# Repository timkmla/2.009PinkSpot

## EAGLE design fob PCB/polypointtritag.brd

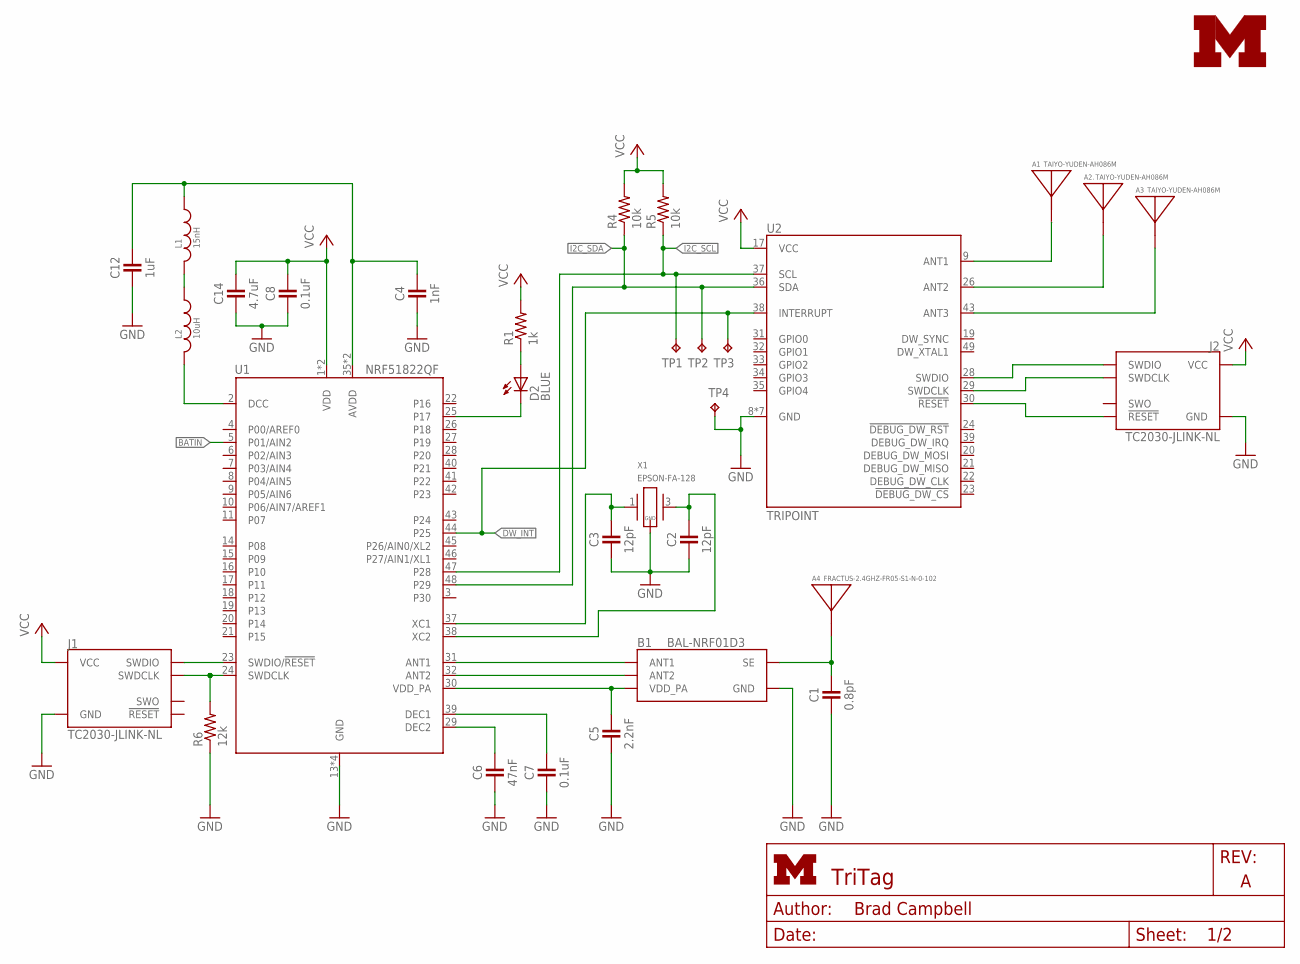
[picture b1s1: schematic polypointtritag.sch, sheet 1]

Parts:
A1, A2., A3: TAIYO-YUDEN-AH086M
A4: FRACTUS-2.4GHZ-FR05-S1-N-0-102; FRACTUS-ANTENNA-FR05-S1-N-0-102
B1: BAL-NRF01D3
C1: 0.8pF; 0402_CAP
C2, C3: 12pF; 0402_CAP
C4: 1nF; 0402_CAP
C5: 2.2nF; 0402_CAP
C6: 47nF; 0402_CAP
C7, C8: 0.1uF; 0402_CAP
C12: 1uF; 0402_CAP
C14: 4.7uF; 0402_CAP
D2: BLUE; LED-0603
J1, J2: TC2030-JLINK-NL; TC2030-IDC-NL
L1: 15nH; 0402_CAP
L2: 10uH; 0603_CAP
LOGO1: UMICH_SOLID_SMALL; UMICH_SOLID_75MIL
R1: 1k; 0402_RES
R4, R5: 10k; 0402_RES
R6: 12k; 0402_RES
TP1, TP2, TP3, TP4: TPTP06SQ; TP06SQ
U1: NRF51822QF; QFN-48-6MM
U2: TRIPOINT
X1: EPSON-FA-128; FA-128

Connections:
!CHRG1: D2.A, R1.1
ANTENNA: A4.1, B1.SE, C1.1
AVDD: C4.1, C12.1, L1.1, U1.35 (AVDD), U1.36 (AVDD)
BATIN: U1.5 (P01/AIN2); also elsewhere on the board
DCC: L2.2, U1.2 (DCC)
DW_INT: TP3.TP, U1.44 (P25), U2.38 (INTERRUPT)
GND: B1.GND, C1.2, C2.2, C3.2, C4.2, C5.2, C6.2, C7.2, C8.2, C12.2, C14.2, J1.5 (GND), J2.5 (GND), R6.1, TP4.TP, U1.13 (GND), U1.33 (GND), U1.34 (GND), U1.GND, U2.8 (GND), U2.10 (GND), U2.18 (GND), U2.25 (GND), U2.27 (GND), U2.42 (GND), U2.44 (GND), X1.2 (GND), X1.4 (GND); also elsewhere on the board
I2C_SCL: R5.1, TP1.TP, U1.47 (P28), U2.37 (SCL)
I2C_SDA: R4.1, TP2.TP, U1.48 (P29), U2.36 (SDA)
unnamed: A1.A, U2.9 (ANT1)
unnamed: A2..A, U2.26 (ANT2)
unnamed: A3.A, U2.43 (ANT3)
unnamed: J2.2 (SWDIO), U2.28 (SWDIO)
unnamed: D2.C, U1.25 (P17)
unnamed: J2.4 (SWDCLK), U2.29 (SWDCLK)
unnamed: J2.3 (!RESET), U2.30 (!RESET)
unnamed: C3.1, U1.37 (XC1), X1.1
unnamed: C2.1, U1.38 (XC2), X1.3 (2)
unnamed: C6.1, U1.29 (DEC2)
unnamed: C7.1, U1.39 (DEC1)
unnamed: B1.ANT1, U1.31 (ANT1)
unnamed: B1.ANT2, U1.32 (ANT2)
unnamed: B1.VCC (VDD_PA), C5.1, U1.30 (VDD_PA)
unnamed: L1.2, L2.1
SWDCLK: J1.4 (SWDCLK), R6.2, U1.24 (SWDCLK)
SWDIO/!RESET: J1.2 (SWDIO), U1.23 (SWDIO/!RESET)
VCC: C8.1, C14.1, J1.1 (VCC), J2.1 (VCC), R1.2, R4.2, R5.2, U1.1 (VDD), U1.12 (VDD), U2.17 (VCC); also elsewhere on the board

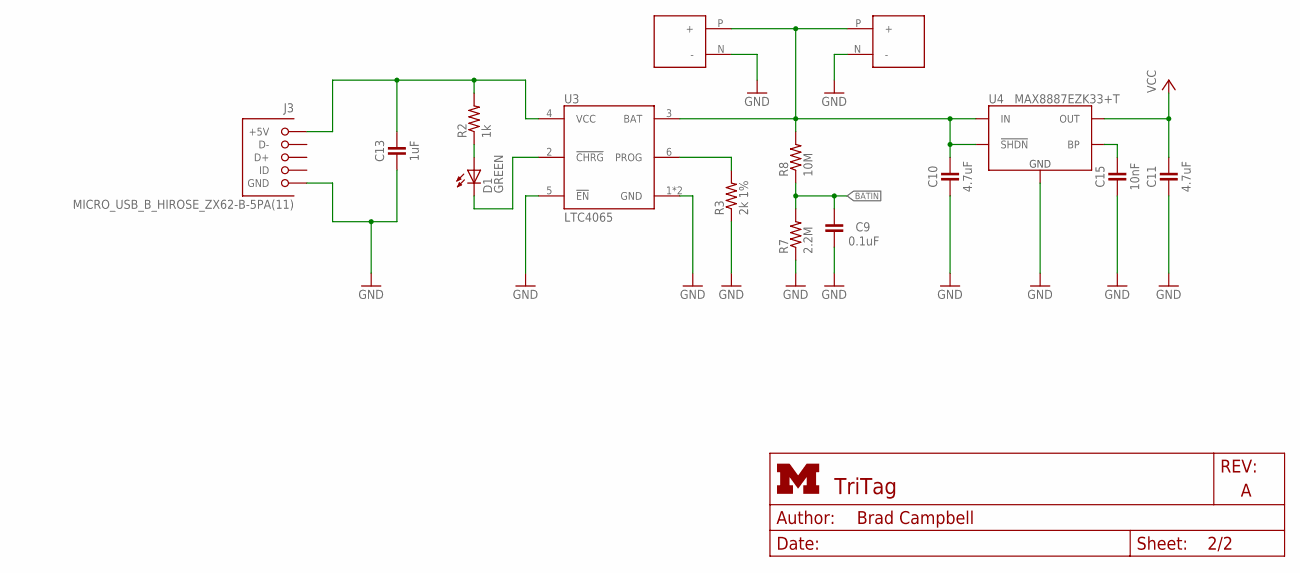
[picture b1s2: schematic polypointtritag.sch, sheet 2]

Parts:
C9: 0.1uF; 0402_CAP
C10, C11: 4.7uF; 0402_CAP
C13: 1uF; 0402_CAP
C15: 10nF; 0402_CAP
D1: GREEN; LED-0603
J3: MICRO_USB_B_HIROSE_ZX62-B-5PA(11); USB_MICRO_B-HIROSE-ZX62-B-5PA(11)
J4, J5: BAT_HOLE; BATTERY_HOLE
R2: 1k; 0402_RES
R3: 2k 1%; 0402_RES
R7: 2.2M; 0402_RES
R8: 10M; 0402_RES
U3: LTC4065; DFN-6/2MM
U4: MAX8887EZK33+T; SOT-23-5

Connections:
!CHRG: D1.A, R2.1
BATIN: C9.2, R7.2, R8.1; also elsewhere on the board
GND: C9.1, C10.2, C11.2, C13.2, C15.2, J3.5 (GND), J4.N (-), J5.N (-), R3.1, R7.1, U3.1 (GND), U3.5 (!EN), U3.7 (GND), U4.2 (GND); also elsewhere on the board
unnamed: D1.C, U3.2 (!CHRG)
unnamed: C15.1, U4.4 (BP)
unnamed: R3.2, U3.6 (PROG)
VBAT: C10.1, J4.P (+), J5.P (+), R8.2, U3.3 (BAT), U4.1 (IN), U4.3 (!SHDN)
VCC: C11.1, U4.5 (OUT); also elsewhere on the board
VUSB: C13.1, J3.1 (+5V), R2.2, U3.4 (VCC)

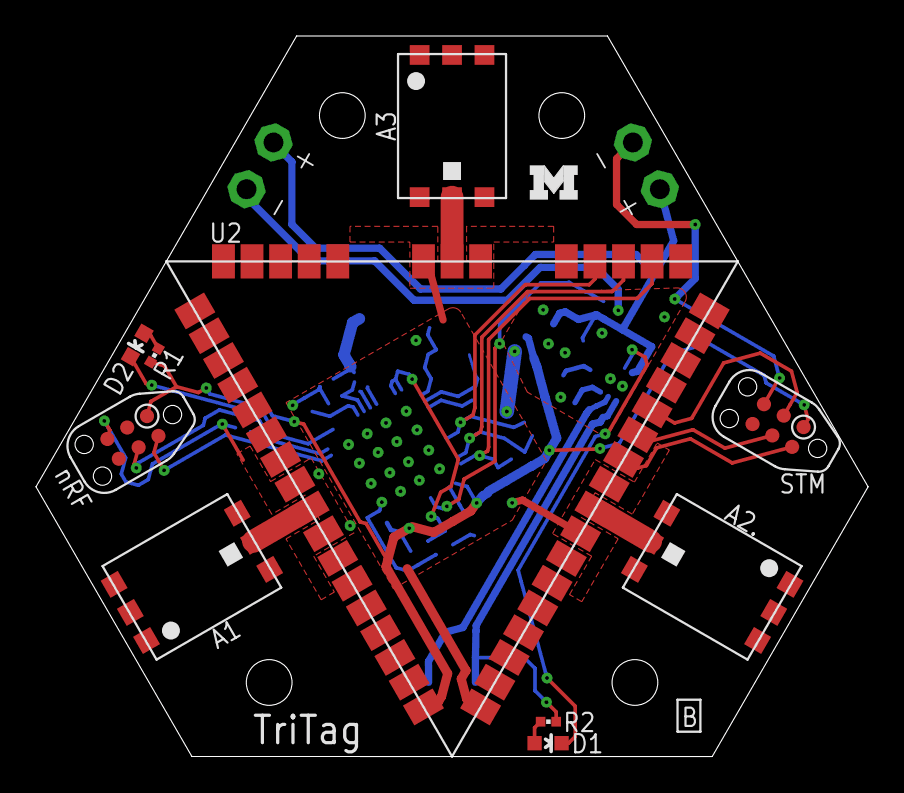
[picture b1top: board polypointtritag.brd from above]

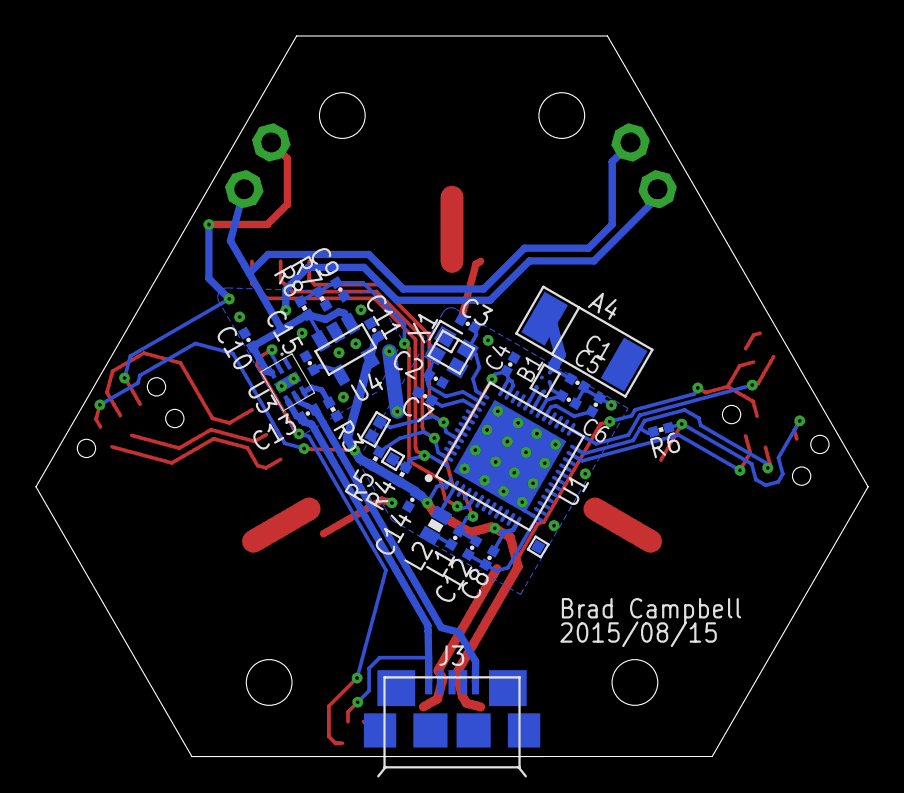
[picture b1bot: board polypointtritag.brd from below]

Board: 2 copper layers, 46.2 x 40.0 mm, 47 parts (34 on the bottom side), 33 nets.

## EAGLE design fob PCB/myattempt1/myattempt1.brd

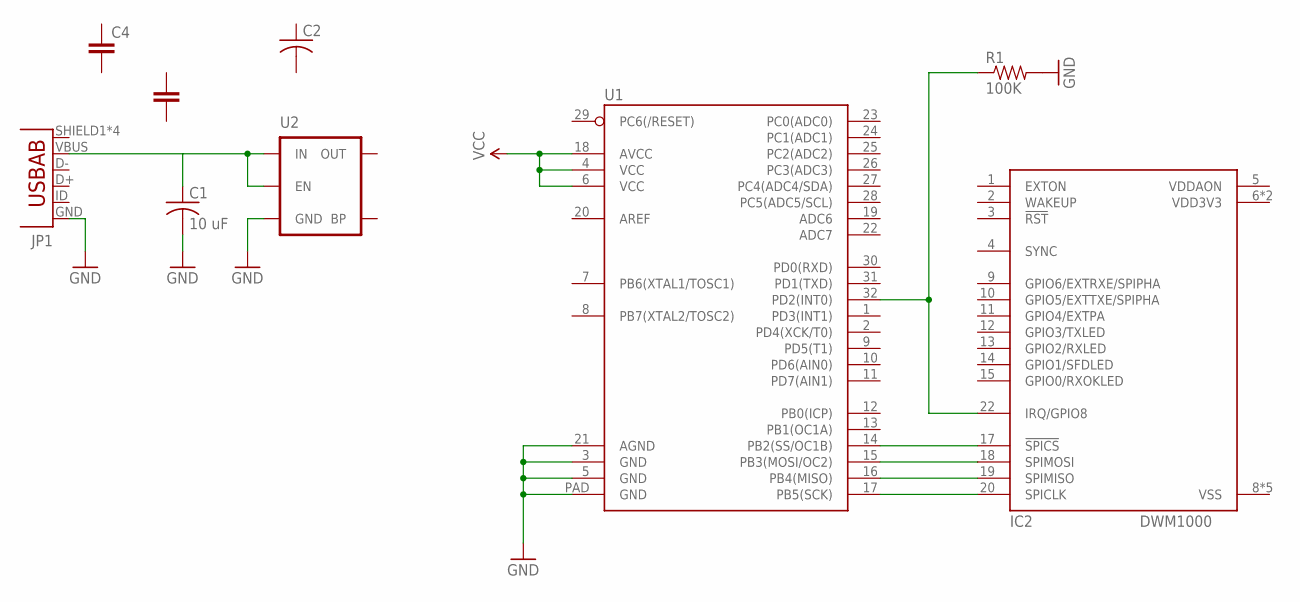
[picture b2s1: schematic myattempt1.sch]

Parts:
C1: 10 uF; C025-024X044
C2: C-US025-024X044; C025-024X044
C4: CAP0402-CAP; 0402-CAP
IC2: DWM1000
JP1: USB-AB; USB-AB-MICRO-SMD
R1: 100K; 0402-RES
U1: ATMEGA328P_MLFMLF32; MLF32-PAD
U2: MIC52053.3V; SOT23-5

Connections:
GND: C1.2, JP1.GND, R1.2, U1.3 (GND), U1.5 (GND), U1.21 (AGND), U1.PAD (GND), U2.2 (GND)
unnamed: IC2.20 (SPICLK), U1.17 (PB5(SCK))
unnamed: IC2.19 (SPIMISO), U1.16 (PB4(MISO))
unnamed: IC2.18 (SPIMOSI), U1.15 (PB3(MOSI/OC2))
unnamed: IC2.22 (IRQ/GPIO8), R1.1, U1.32 (PD2(INT0))
unnamed: IC2.17 (!SPICS), U1.14 (PB2(SS/OC1B))
unnamed: C1.1, JP1.VBUS, U2.1 (IN), U2.3 (EN)
VCC: U1.4 (VCC), U1.6 (VCC), U1.18 (AVCC)

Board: 2 copper layers, 8 parts (0 on the bottom side), 8 nets, no tracks yet.

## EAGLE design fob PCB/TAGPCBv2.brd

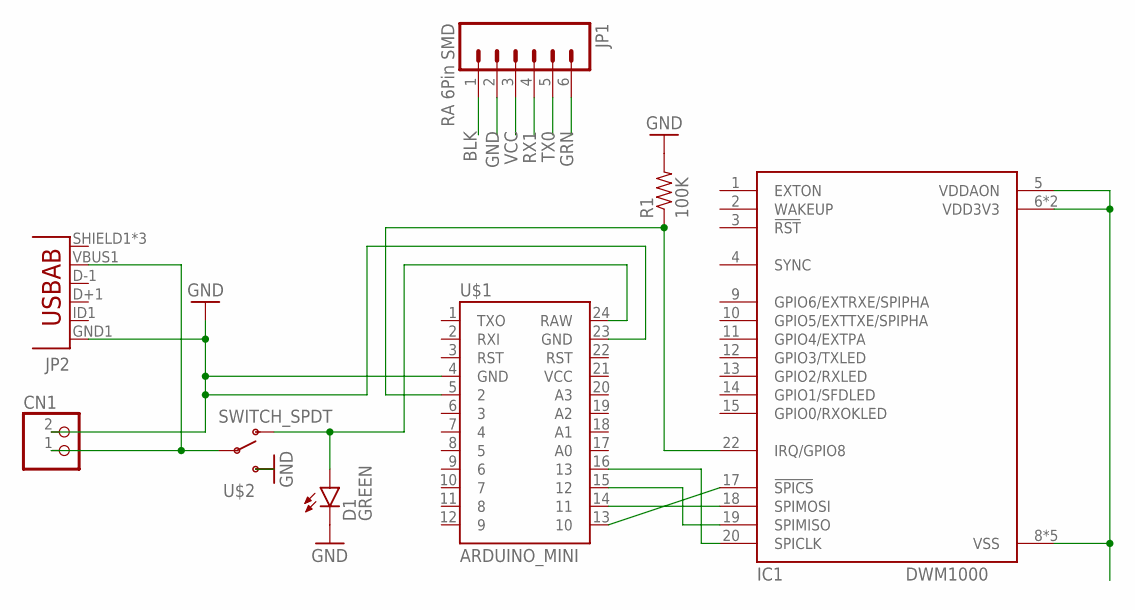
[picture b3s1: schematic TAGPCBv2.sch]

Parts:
CN1: JST_2PIN-SMT-RA; JST-PH-2-SMT-RA
D1: GREEN; LED-0603
IC1: DWM1000
JP1: RA 6Pin SMD; 1X06-SMD
JP2: USB-ABCONN-11794; USB-AB-MICRO-SMD_V03
R1: 100K; AXIAL-0.3
U$1: ARDUINO_MINI
U$2: SWITCH_SPDT; KPS-1290

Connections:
BLK: JP1.1
GND: CN1.2 (1), D1.C, JP1.2, JP2.GND1 (GND), R1.P$2 (2), U$1.4 (GND), U$1.23 (GND), U$2.S
GRN: JP1.6
unnamed: IC1.17 (!SPICS), U$1.13 (10)
unnamed: IC1.22 (IRQ/GPIO8), R1.P$1 (1), U$1.5 (2)
unnamed: IC1.18 (SPIMOSI), U$1.14 (11)
unnamed: IC1.19 (SPIMISO), U$1.15 (12)
unnamed: IC1.20 (SPICLK), U$1.16 (13)
unnamed: D1.A, U$1.24 (RAW), U$2.O
unnamed: CN1.1 (2), JP2.VBUS1 (VBUS), U$2.P
unnamed: IC1.5 (VDDAON), IC1.6 (VDD3V3), IC1.7 (VDD3V3), IC1.8 (VSS), IC1.16 (VSS), IC1.21 (VSS), IC1.23 (VSS), IC1.24 (VSS)
RX1: JP1.4
TX0: JP1.5
VCC: JP1.3

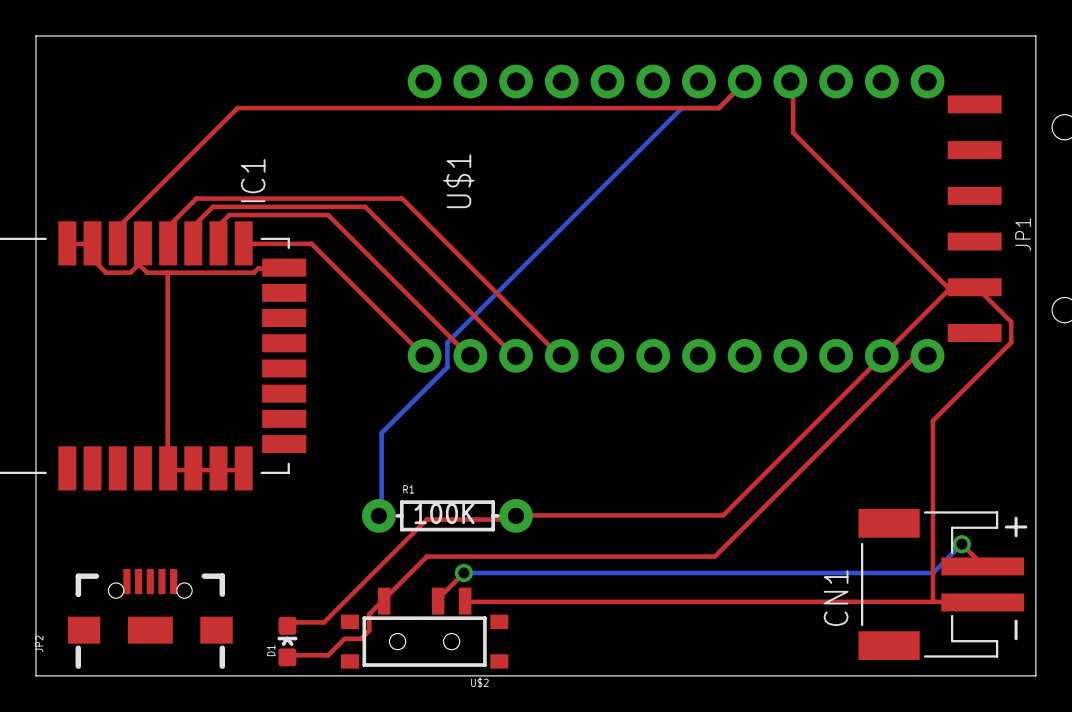
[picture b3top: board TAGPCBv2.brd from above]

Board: 4 copper layers, 55.5 x 35.5 mm, 8 parts (0 on the bottom side), 9 nets.

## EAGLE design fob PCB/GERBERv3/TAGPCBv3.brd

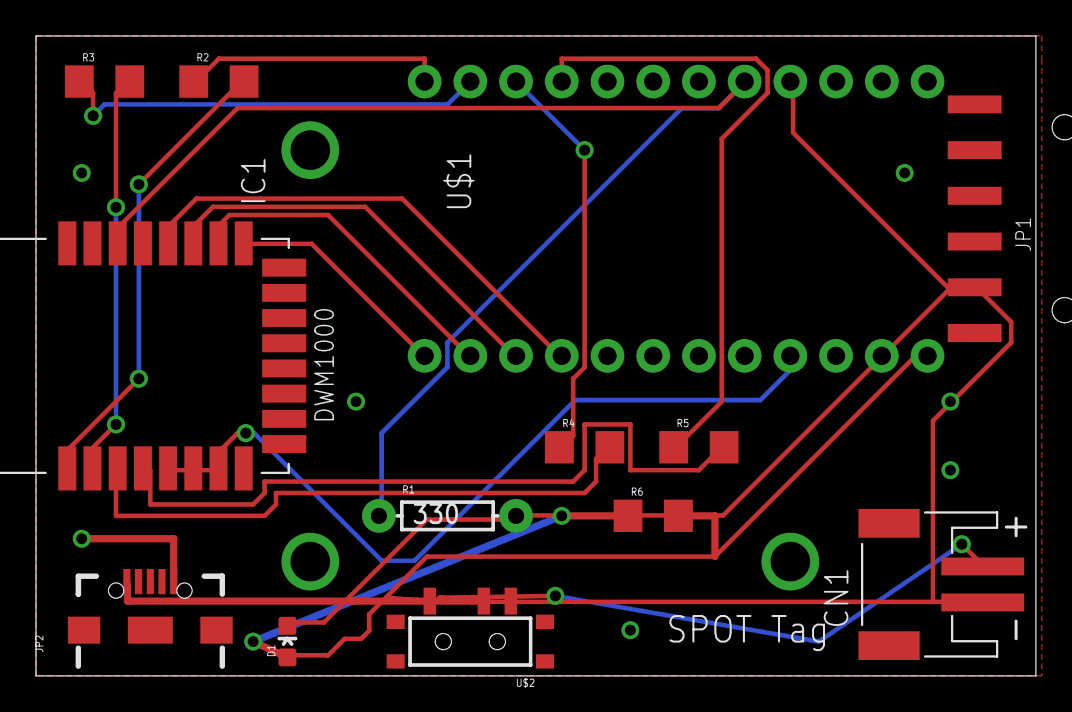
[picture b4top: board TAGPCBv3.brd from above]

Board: 2 copper layers, 55.5 x 35.5 mm, 13 parts (0 on the bottom side), 18 nets.

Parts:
CN1: JST-PH-2-SMT-RA
D1: GREEN; LED-0603
IC1: DWM1000
JP1: RA 6Pin SMD; 1X06-SMD
JP2: USB-AB-MICRO-SMD_V03
R1: 330; AXIAL-0.3
R2, R3, R5: 0R; 1206
R4: 100K; 1206
R6: 1K; 1206
U$1: ARDUINO_MINI
U$2: SWITCH_SPDT; KPS-1290

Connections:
GND: CN1.2, D1.C, IC1.8, IC1.16, IC1.21, IC1.23, IC1.24, JP1.2, JP2.GND1, R1.P$2, U$1.4, U$1.23
unnamed: IC1.17, U$1.13
unnamed: IC1.22, R1.P$1, U$1.5
unnamed: IC1.18, U$1.14
unnamed: IC1.19, U$1.15
unnamed: IC1.20, U$1.16
unnamed: R6.2, U$1.24, U$2.O
unnamed: CN1.1, JP2.VBUS1, U$2.P
unnamed: IC1.5, IC1.6, IC1.7, U$1.21
unnamed: R2.1, U$1.12
unnamed: IC1.1, R2.2
unnamed: R3.1, U$1.11
unnamed: IC1.2, R3.2
unnamed: IC1.3, R4.2
unnamed: R4.1, U$1.10
unnamed: R5.1, U$1.9
unnamed: IC1.4, R5.2
unnamed: D1.A, R6.1

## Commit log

2015-11-05 calibrationCode
    calibration code which solves for the height of the light
2015-11-19 fob PCB
2015-11-19 Eurah's test files.
2015-11-19 testing to make sure my ssh key works
2015-11-19 deleting test files
2015-11-19 Consolidated_reading_tracking_writing_V3.py
2015-11-19 ZipliteStepperControl
2015-11-19 ZipliteStepperControlBoth
2015-11-19 fob PCB Updated
2015-11-20 Create PIDPseudoCode
2015-11-21 python -> DMX script for duPlessie's minimac
2015-11-22 need to add this library in super duper hacky manner, refer to Eurah
2015-11-22 not much has changed
2015-11-22 getting rid of that file
2015-11-22 new test file for dmx
2015-11-22 before leaving to E33
2015-11-22 changing position for one time works, currently does not work with changes in succession

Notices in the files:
parts and their libraries:
SparkFun-Boards: Licensing: Creative Commons ShareAlike 4.0 International - https://creativecommons.org/licenses/by-sa/4.0
SparkFun-LED: Licensing: CC v3.0 Share-Alike You are welcome to use this library for commercial purposes.
